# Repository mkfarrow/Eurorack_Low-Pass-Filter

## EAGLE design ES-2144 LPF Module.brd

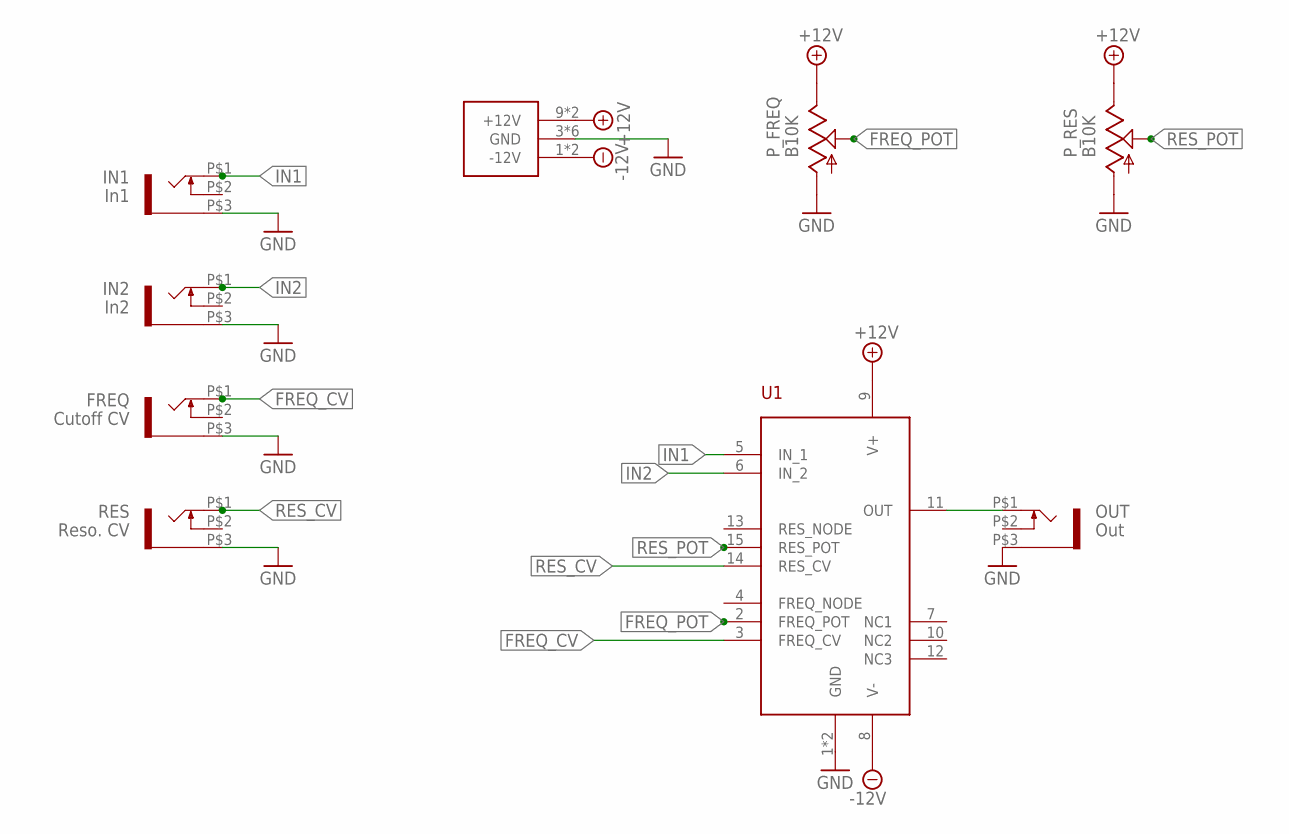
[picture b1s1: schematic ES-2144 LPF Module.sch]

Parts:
FREQ: Cutoff CV; THONKICONN_WQP-PJ301M-12_JACK
IN1: In1; THONKICONN_WQP-PJ301M-12_JACK
IN2: In2; THONKICONN_WQP-PJ301M-12_JACK
OUT: Out; THONKICONN_WQP-PJ301M-12_JACK
P_FREQ: B10K; MUSICTHINGMODULAR_9MM_SNAP-IN_POT
P_RES: B10K; MUSICTHINGMODULAR_9MM_SNAP-IN_POT
RES: Reso. CV; THONKICONN_WQP-PJ301M-12_JACK
U1: ES_2144_V2
U$1: POWER_SIMPLE10; POWER_10

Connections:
+12V: P_FREQ.3 (E), P_RES.3 (E), U1.9 (V+), U$1.9 (+12V), U$1.10 (+12V)
-12V: U1.8 (V-), U$1.1 (-12V), U$1.2 (-12V)
FREQ_CV: FREQ.P$1 (2), U1.3 (FREQ_CV)
FREQ_POT: P_FREQ.2 (S), U1.2 (FREQ_POT)
GND: FREQ.P$3 (1), IN1.P$3 (1), IN2.P$3 (1), OUT.P$3 (1), P_FREQ.1 (A), P_RES.1 (A), RES.P$3 (1), U1.1 (GND), U1.16 (GND), U$1.3 (GND), U$1.4 (GND), U$1.5 (GND), U$1.6 (GND), U$1.7 (GND), U$1.8 (GND)
IN1: IN1.P$1 (2), U1.5 (IN_1)
IN2: IN2.P$1 (2), U1.6 (IN_2)
unnamed: OUT.P$1 (2), U1.11 (OUT)
RES_CV: RES.P$1 (2), U1.14 (RES_CV)
RES_POT: P_RES.2 (S), U1.15 (RES_POT)

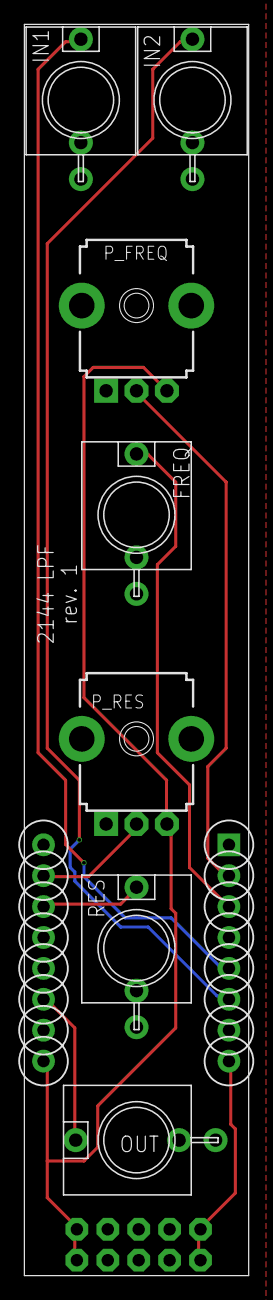
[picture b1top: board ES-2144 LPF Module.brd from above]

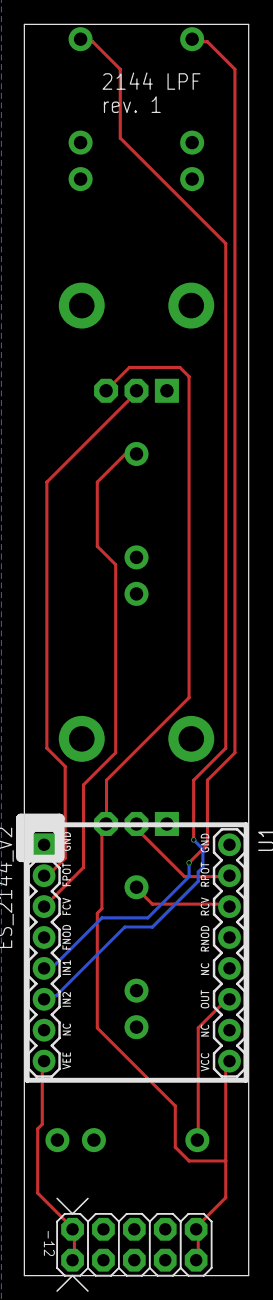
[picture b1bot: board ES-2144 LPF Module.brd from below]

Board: 2 copper layers, 18.4 x 102.8 mm, 9 parts (2 on the bottom side), 10 nets.

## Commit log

2022-06-10 added cad files
2022-12-22 adding images
